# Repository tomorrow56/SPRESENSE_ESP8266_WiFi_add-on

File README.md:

# SPRESENSE Wi-Fi Add-on

 [English](README_EN.md)

## 概要
Sonyの省電力で高性能なIoT開発ボードSPRESENSEにWi-FI機能を追加するためのアドオンボードです。
ESP8266(ESP-WROOM-02, 技適取得済)を搭載、SPRESENSEとEP8266の間の通信は [Espressif標準のATコマンド](ESP8266_AT_command/) を使用します。

## 主な仕様
- ESP8266(ESP-WROOM-02)を搭載
- SPRESENSEメインボード上面の拡張コネクタに直接装着可能（レベルシフタ搭載）
- ハーフサイズ設計で他のハーフサイズモジュールと同時に使用可能
- I2C・SPI接続のモジュールとの同時使用が可能（一部制限あり）
- 技適取得済み

### v2.2について(2026年1月リリース)
従来のバージョン(v1.1)と比較して、以下の変更があります：
- ESP8266 Deep sleep機能への対応

この対応のため、リセット回路の設計を変更しました。そのため、従来のv1.1のソフトウエアを使用する場合は、以下のリセットピン(D21)の制御の追加が必要となります。

```cpp
#define rst_pin PIN_D21   // ESP8266のリセットピン, Hでリセット

void setup() {
  // ESP8266のリセットピンの設定
  pinMode(rst_pin, OUTPUT);
  // ESP8266のリセットを解除する(リセットピンをLにする)
  digitalWrite(rst_pin, LOW);

```

## 製品画像 (基板の色は予告なく変更になる場合があります)

### v1.1

#### 基板表面

#### 基板裏面

#### SPRESENSEへ取り付けた状態 (SPRESENSEは付属しません)

### v2.2

#### 基板表面

#### 基板裏面

#### SPRESENSEへ取り付けた状態 (SPRESENSEは付属しません)

## 回路図

### v1.1回路図

### v2.2回路図

## 基板設計データ

基板設計データはKiCadプロジェクト形式で提供されています。
- v1.1: `kicad/v1.1/`
- v2.2: `kicad/v2.2/`

各バージョンの基板設計データには、回路図、PCBレイアウト、部品リストなどが含まれています。

## サンプルコード

各バージョンのサンプルコードは、`example/`ディレクトリ以下に格納されています。
- v1.1: `example/v1.1/`
- v2.2: `example/v2.2/`

各サンプルコードは、SPRESENSEのArduino IDE環境で動作するように設計されています。
詳細な使用方法は各サンプルコードのコメントを参照してください。

## ライセンス

このプロジェクトはGNU General Public License v3.0ライセンスの下で提供されます。詳細は[LICENSE](LICENSE)ファイルを参照してください。

## 作者

- [tomorrow56](https://github.com/tomorrow56)

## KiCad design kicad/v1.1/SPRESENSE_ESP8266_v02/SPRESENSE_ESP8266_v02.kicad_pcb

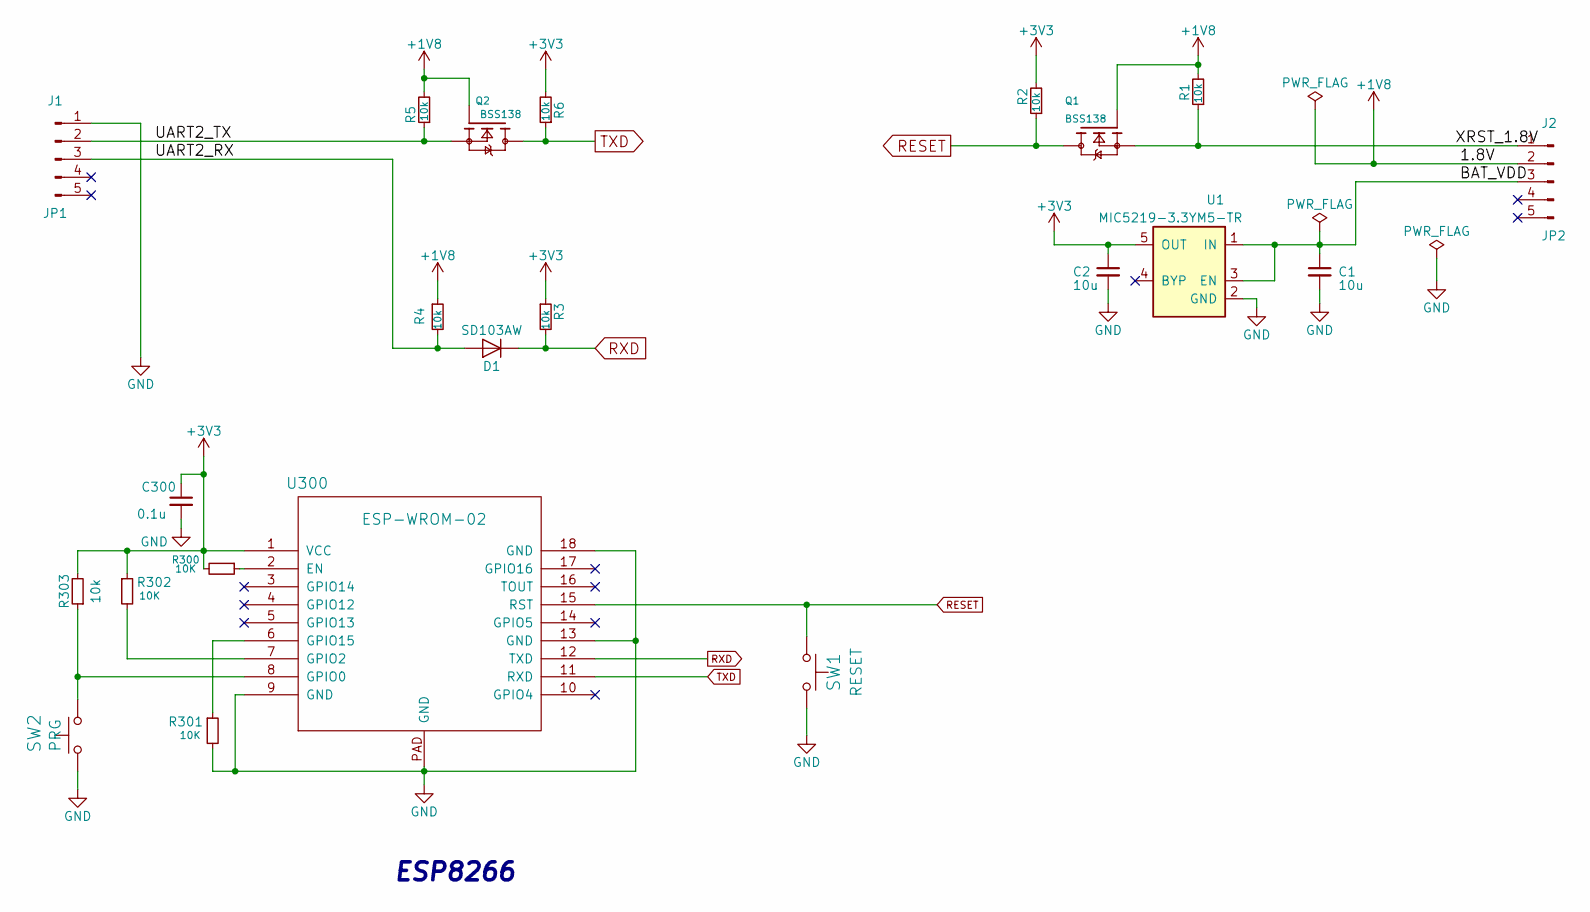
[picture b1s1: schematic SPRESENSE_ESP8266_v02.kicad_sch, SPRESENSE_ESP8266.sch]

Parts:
C1, C2: 10u; C_0603
C300: 0.1u; C_0603
D1: SD103AW; D_SOD-123F
J1: JP1; Pin_Header_Straight_1x05_Pitch2.54mm_SMD_Pin1Right
J2: JP2; Pin_Header_Straight_1x05_Pitch2.54mm_SMD_Pin1Left
Q1, Q2: BSS138; SOT-23
R1, R2, R3, R4, R5, R6, R303: 10k; R_0603
R300, R301, R302: 10K; R_0603
SW1: RESET; SW_SPST_PTS810
SW2: PRG; SW_SPST_PTS810
U1: MIC5219-3.3YM5-TR; SOT-23-5
U300: ESP-WROM-02; ESP-13-WROOM-02

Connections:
+1V8: J2.2, Q1.1 (G), Q2.1 (G), R1.2, R4.1, R5.2
+3V3: C2.1, C300.1, R2.2, R3.1, R6.2, R300.2, R302.1, R303.2, U1.5 (OUT), U300.1 (VCC)
/BAT_VDD: C1.1, J2.3, U1.1 (IN), U1.3 (EN)
/UART2_RX: D1.2 (A), J1.3, R4.2
/UART2_TX: J1.2, Q2.2 (S), R5.1
/XRST_1.8V: J2.1, Q1.2 (S), R1.1
GND: C1.2, C2.2, C300.2, J1.1, R301.2, SW1.1, SW2.1, U1.2 (GND), U300.9 (GND), U300.13 (GND), U300.18 (GND), U300.PAD (GND)
unnamed: R300.1, U300.2 (EN)
unnamed: R301.1, U300.6 (GPIO15)
unnamed: R302.2, U300.7 (GPIO2)
unnamed: R303.1, SW2.2, U300.8 (GPIO0)
RESET: Q1.3 (D), R2.1, SW1.2, U300.15 (RST)
RXD: D1.1 (K), R3.2, U300.12 (TXD)
TXD: Q2.3 (D), R6.1, U300.11 (RXD)

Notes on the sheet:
ESP8266

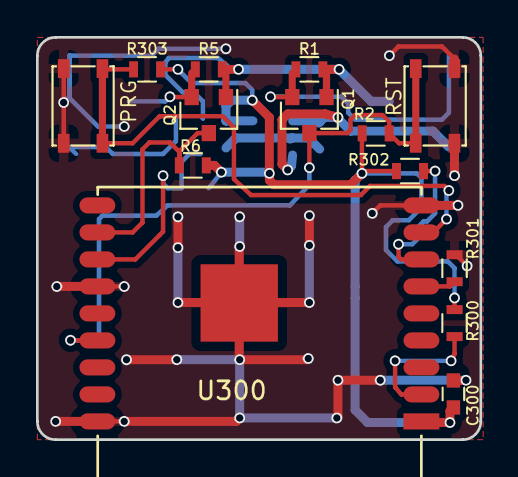
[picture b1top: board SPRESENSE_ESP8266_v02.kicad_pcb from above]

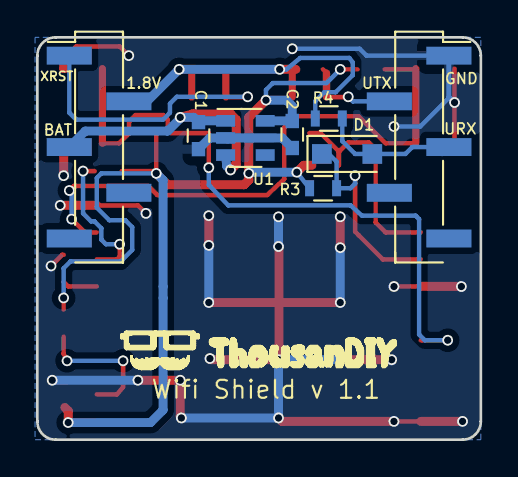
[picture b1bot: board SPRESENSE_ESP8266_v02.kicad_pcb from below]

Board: 2 copper layers, 24.6 x 22.4 mm, 23 parts (9 on the bottom side), 14 nets.

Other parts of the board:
ref**: val**; TDIY-LOGO-S

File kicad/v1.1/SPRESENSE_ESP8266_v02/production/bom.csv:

Designator,Footprint,Quantity,Value,LCSC Part #
"C1, C2",C_0603,2,10u,
C300,C_0603,1,0.1u,
D1,D_SOD-123F,1,SD103AW,
J1,Pin_Header_Straight_1x05_Pitch2.54mm_SMD_Pin1Right,1,JP1,
J2,Pin_Header_Straight_1x05_Pitch2.54mm_SMD_Pin1Left,1,JP2,
"Q1, Q2",SOT-23,2,BSS138,
"R1, R2, R3, R300, R301, R302, R303, R4, R5, R6",R_0603,10,10k,
SW1,SW_SPST_PTS810,1,RESET,
SW2,SW_SPST_PTS810,1,PRG,
U1,SOT-23-5,1,MIC5219-3.3BM5,
U300,ESP-13-WROOM-02,1,ESP-WROM-02,

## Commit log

2026-01-04 Refactor: Reorganize repository structure and add English README
    - Add .gitignore to exclude macOS metadata and backup files
    - Add README_EN.md with English translation and cross-link
    - Move AT command PDFs to ESP8266_AT_command/ directory
    - Reorganize examples under versioned directories (v1.1/, v2.2/)
    - Add v2.2 examples with LINE messaging API and PIR sensor demo
    - Move KiCad files to versioned directories and add v2.2 schematics
2026-01-04 Add .vscode/ to .gitignore to exclude IDE settings
2026-01-04 Add Board Design Data section to README_EN.md
    - Mirror the Japanese README.md addition
    - Include section explaining KiCad project locations and contents
2026-01-04 Move library/SparkFun_ESP8266_AT_Arduino_Library to example/v1.1/library/
    - Reorganize library under versioned example structure
    - Maintains all library files and examples within v1.1 directory
2026-01-04 Add English version of example/v2.2/README.md
    - Create README_EN.md with complete English translation
    - Add cross-language links between Japanese and English versions
    - Maintain consistent documentation structure
2026-01-04 Add README files for example/v1.1/
    - Create comprehensive Japanese README.md with v1.1 sample descriptions
    - Create English README_EN.md with complete translation
    - Add cross-language links between both versions
    - Document all 6 sample programs and library usage
    - Include hardware requirements and configuration instructions
